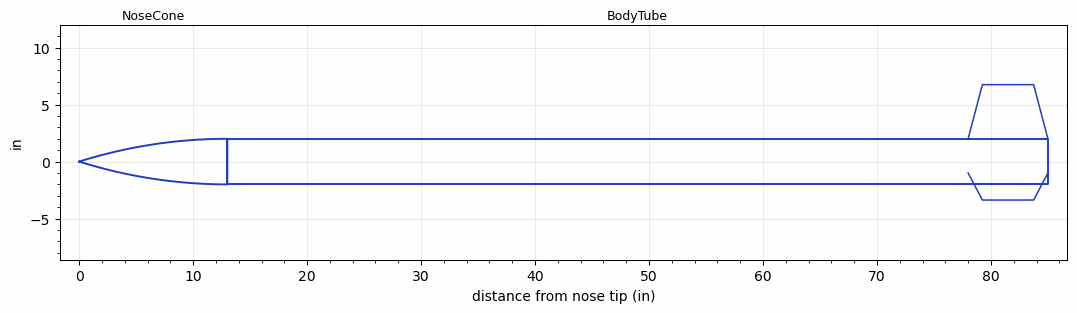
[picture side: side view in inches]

<RASAeroDocument>
 <FileVersion>2</FileVersion>
 <RocketDesign>
  <NoseCone>
   <Length>13</Length>
   <Diameter>4</Diameter>
   <Shape>Tangent Ogive</Shape>
   <Location>0</Location>
  </NoseCone>
  <BodyTube>
   <Length>72</Length>
   <Diameter>4</Diameter>
   <RailGuideDiameter>0.625</RailGuideDiameter>
   <RailGuideHeight>0.469</RailGuideHeight>
   <Location>13</Location>
   <Fin>
    <Count>3</Count>
    <Chord>7</Chord>
    <Span>4.75</Span>
    <SweepDistance>1.25</SweepDistance>
    <TipChord>4.5</TipChord>
    <Thickness>0.25</Thickness>
    <Location>7</Location>
    <AirfoilSection>Rounded</AirfoilSection>
    <FX1>0.25</FX1>
   </Fin>
  </BodyTube>
  <Surface>Smooth (Zero Roughness)</Surface>
  <ModifiedBarrowman>False</ModifiedBarrowman>
  <Turbulence>False</Turbulence>
  <UseBooster1>False</UseBooster1>
  <UseBooster2>False</UseBooster2>
  <Comments>LOC/Precision EZI-65   J450ST Animal Motor Works
LDRS-26
Jean Dry Lake

Barometric Altimeter
Altitude = 3965 ft

RASAero Prediction = 4214 ft
Error = 6.28%
</Comments>
 </RocketDesign>
 <LaunchSite>
  <Altitude>2750</Altitude>
  <Pressure>0</Pressure>
  <RodAngle>0</RodAngle>
  <RodLength>10</RodLength>
  <Temperature>70</Temperature>
  <WindSpeed>0</WindSpeed>
 </LaunchSite>
 <Recovery>
  <Altitude1>1000</Altitude1>
  <Altitude2>1000</Altitude2>
  <DeviceType1>None</DeviceType1>
  <DeviceType2>None</DeviceType2>
  <Event1>False</Event1>
  <Event2>False</Event2>
  <Size1>1</Size1>
  <Size2>1</Size2>
  <EventType1>None</EventType1>
  <EventType2>None</EventType2>
  <CD1>1.33</CD1>
  <CD2>1.33</CD2>
 </Recovery>
 <SimulationList>
  <Simulation>
   <SustainerEngine>J450ST  (AMW)</SustainerEngine>
   <SustainerLaunchWt>10.06</SustainerLaunchWt>
   <SustainerCG>59</SustainerCG>
   <SustainerIgnitionDelay>0</SustainerIgnitionDelay>
   <Booster1SeparationDelay>0</Booster1SeparationDelay>
   <Booster1IgnitionDelay>0</Booster1IgnitionDelay>
   <IncludeBooster1>False</IncludeBooster1>
   <Booster2Delay>0</Booster2Delay>
   <IncludeBooster2>False</IncludeBooster2>
   <TimetoApogee>15.38026</TimetoApogee>
   <MaxAltitude>4214.14</MaxAltitude>
   <MaxVelocity>675.9597</MaxVelocity>
  </Simulation>
 </SimulationList>
</RASAeroDocument>
